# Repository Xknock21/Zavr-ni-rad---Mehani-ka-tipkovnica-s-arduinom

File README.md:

# Zavrsni rad Mehanicka tipkovnica s arduinom

<h3>Shema</h3>

Shema tipkovnicje korisit matriks koji gleda koja je tipka pritisnuta u bilo kojem vrenu te ta se informacija šalje arduinu te on računalu šalje podatak koja je tipka pritisnuta i što bi on trebao ispisati.

<h3>PCB</h3> 

Napravio sam PCB-u besplatnom programu KiCad 7.0, a izradu PCB-a je odradio JLCPCB.

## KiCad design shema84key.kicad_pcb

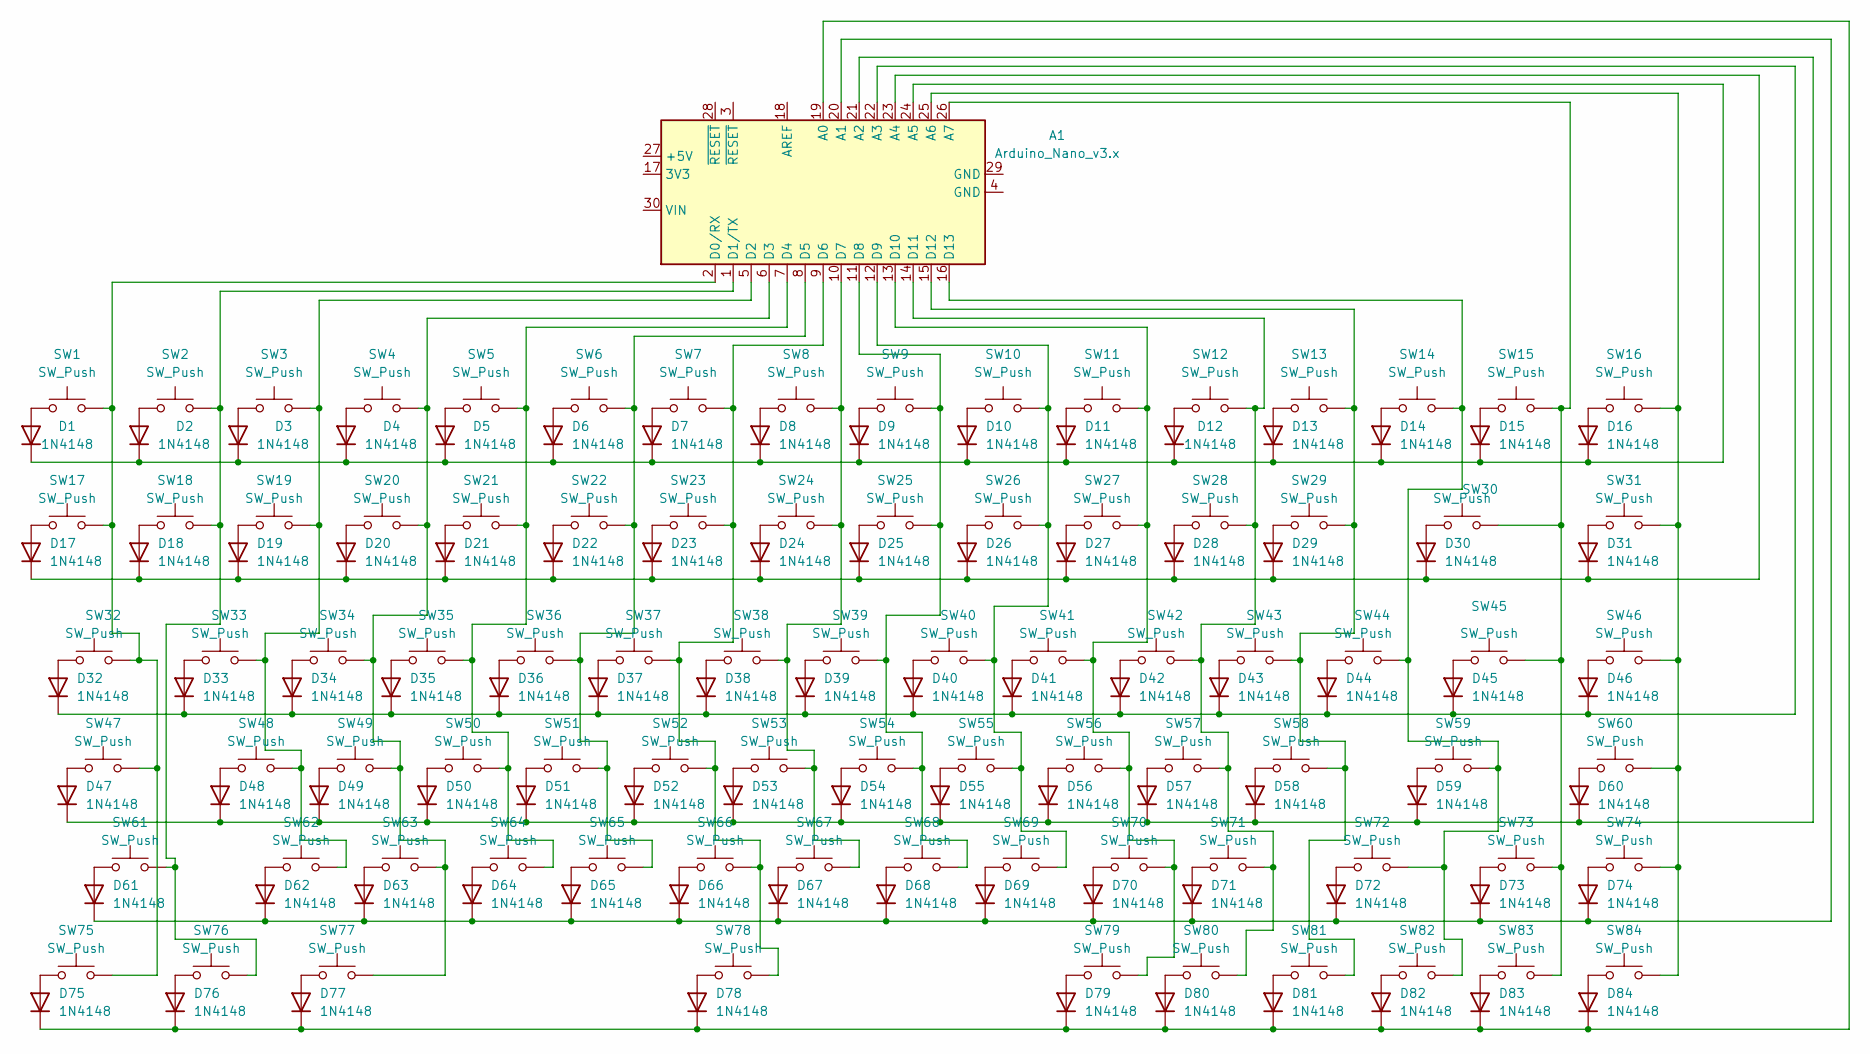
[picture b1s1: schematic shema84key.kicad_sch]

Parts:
A1: Arduino_Nano_v3.x; Arduino_Nano
D1, D2, D3, D4, D5, D6, D7, D8, D9, D10, D11, D12, D13, D14, D15, D16, D17, D18, D19, D20, D21, D22, D23, D24, D25, D26, D27, D28, D29, D30, D31, D32, D33, D34, D35, D36, D37, D38, D39, D40, D41, D42, D43, D44, D45, D46, D47, D48, D49, D50, D51, D52, D53, D54, D55, D56, D57, D58, D59, D60, D61, D62, D63, D64, D65, D66, D67, D68, D69, D70, D71, D72, D73, D74, D75, D76, D77, D78, D79, D80, D81, D82, D83, D84: 1N4148; D_DO-35_SOD27_P7.62mm_Horizontal
SW1, SW2, SW3, SW4, SW5, SW6, SW7, SW8, SW9, SW10, SW11, SW12, SW13, SW14, SW15, SW16, SW17, SW18, SW19, SW20, SW21, SW22, SW23, SW24, SW25, SW26, SW27, SW28, SW29, SW31, SW33, SW34, SW35, SW36, SW37, SW38, SW39, SW40, SW41, SW42, SW43, SW44, SW46, SW48, SW49, SW50, SW51, SW52, SW53, SW54, SW55, SW56, SW57, SW58, SW60, SW62, SW63, SW64, SW65, SW66, SW67, SW68, SW69, SW70, SW71, SW73, SW74, SW79, SW80, SW81, SW82, SW83, SW84: SW_Push; SW_Cherry_MX_1.00u_PCB
SW30: SW_Push; SW_Cherry_MX_2.00u_PCB
SW32, SW45: SW_Push; SW_Cherry_MX_1.50u_PCB
SW47, SW72: SW_Push; SW_Cherry_MX_1.75u_PCB
SW59, SW61: SW_Push; SW_Cherry_MX_2.25u_PCB
SW75, SW76, SW77: SW_Push; SW_Cherry_MX_1.25u_PCB
SW78: SW_Push; SW_Cherry_MX_6.25u_PCB

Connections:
unnamed: A1.19 (A0), D75.1 (K), D76.1 (K), D77.1 (K), D78.1 (K), D79.1 (K), D80.1 (K), D81.1 (K), D82.1 (K), D83.1 (K), D84.1 (K)
unnamed: A1.20 (A1), D61.1 (K), D62.1 (K), D63.1 (K), D64.1 (K), D65.1 (K), D66.1 (K), D67.1 (K), D68.1 (K), D69.1 (K), D70.1 (K), D71.1 (K), D72.1 (K), D73.1 (K), D74.1 (K)
unnamed: A1.21 (A2), D47.1 (K), D48.1 (K), D49.1 (K), D50.1 (K), D51.1 (K), D52.1 (K), D53.1 (K), D54.1 (K), D55.1 (K), D56.1 (K), D57.1 (K), D58.1 (K), D59.1 (K), D60.1 (K)
unnamed: A1.22 (A3), D32.1 (K), D33.1 (K), D34.1 (K), D35.1 (K), D36.1 (K), D37.1 (K), D38.1 (K), D39.1 (K), D40.1 (K), D41.1 (K), D42.1 (K), D43.1 (K), D44.1 (K), D45.1 (K), D46.1 (K)
unnamed: A1.23 (A4), D17.1 (K), D18.1 (K), D19.1 (K), D20.1 (K), D21.1 (K), D22.1 (K), D23.1 (K), D24.1 (K), D25.1 (K), D26.1 (K), D27.1 (K), D28.1 (K), D29.1 (K), D30.1 (K), D31.1 (K)
unnamed: A1.24 (A5), D1.1 (K), D2.1 (K), D3.1 (K), D4.1 (K), D5.1 (K), D6.1 (K), D7.1 (K), D8.1 (K), D9.1 (K), D10.1 (K), D11.1 (K), D12.1 (K), D13.1 (K), D14.1 (K), D15.1 (K), D16.1 (K)
unnamed: A1.25 (A6), SW16.2, SW31.2, SW46.2, SW60.2, SW74.2, SW84.2
unnamed: A1.2 (D0/RX), SW1.2, SW17.2, SW32.2, SW47.2, SW75.2
unnamed: A1.1 (D1/TX), SW2.2, SW18.2, SW61.2, SW76.2
unnamed: A1.5 (D2), SW3.2, SW19.2, SW33.2, SW48.2, SW62.2
unnamed: A1.6 (D3), SW4.2, SW20.2, SW34.2, SW49.2, SW63.2, SW77.2
unnamed: A1.7 (D4), SW5.2, SW21.2, SW35.2, SW50.2, SW64.2
unnamed: A1.8 (D5), SW6.2, SW22.2, SW36.2, SW51.2, SW65.2
unnamed: A1.9 (D6), SW7.2, SW23.2, SW37.2, SW52.2, SW66.2, SW78.2
unnamed: A1.10 (D7), SW8.2, SW24.2, SW38.2, SW53.2, SW67.2
unnamed: A1.11 (D8), SW9.2, SW25.2, SW39.2, SW54.2, SW68.2
unnamed: A1.12 (D9), SW10.2, SW26.2, SW40.2, SW55.2, SW69.2
unnamed: A1.13 (D10), SW11.2, SW27.2, SW41.2, SW56.2, SW70.2, SW79.2
unnamed: A1.14 (D11), SW12.2, SW28.2, SW42.2, SW57.2, SW71.2, SW80.2
unnamed: A1.15 (D12), SW13.2, SW29.2, SW43.2, SW58.2, SW81.2
unnamed: A1.16 (D13), SW14.2, SW44.2, SW59.2, SW72.2, SW82.2
unnamed: D1.2 (A), SW1.1
unnamed: D2.2 (A), SW2.1
unnamed: D3.2 (A), SW3.1
unnamed: D4.2 (A), SW4.1
unnamed: D5.2 (A), SW5.1
unnamed: D6.2 (A), SW6.1
unnamed: D7.2 (A), SW7.1
unnamed: D8.2 (A), SW8.1
unnamed: D9.2 (A), SW9.1
unnamed: D10.2 (A), SW10.1
unnamed: D11.2 (A), SW11.1
unnamed: D12.2 (A), SW12.1
unnamed: D13.2 (A), SW13.1
unnamed: D14.2 (A), SW14.1
unnamed: D15.2 (A), SW15.1
unnamed: D16.2 (A), SW16.1
unnamed: D17.2 (A), SW17.1
unnamed: D18.2 (A), SW18.1
unnamed: D19.2 (A), SW19.1
unnamed: D20.2 (A), SW20.1
unnamed: D21.2 (A), SW21.1
unnamed: D22.2 (A), SW22.1
unnamed: D23.2 (A), SW23.1
unnamed: D24.2 (A), SW24.1
unnamed: D25.2 (A), SW25.1
unnamed: D26.2 (A), SW26.1
unnamed: D27.2 (A), SW27.1
unnamed: D28.2 (A), SW28.1
unnamed: D29.2 (A), SW29.1
unnamed: D30.2 (A), SW30.1
unnamed: D31.2 (A), SW31.1
unnamed: D32.2 (A), SW32.1
unnamed: D33.2 (A), SW33.1
unnamed: D34.2 (A), SW34.1
unnamed: D35.2 (A), SW35.1
unnamed: D36.2 (A), SW36.1
unnamed: D37.2 (A), SW37.1
unnamed: D38.2 (A), SW38.1
unnamed: D39.2 (A), SW39.1
unnamed: D40.2 (A), SW40.1
unnamed: D41.2 (A), SW41.1
unnamed: D42.2 (A), SW42.1
unnamed: D43.2 (A), SW43.1
unnamed: D44.2 (A), SW44.1
unnamed: D45.2 (A), SW45.1
unnamed: D46.2 (A), SW46.1
unnamed: D47.2 (A), SW47.1
unnamed: D48.2 (A), SW48.1
unnamed: D49.2 (A), SW49.1
unnamed: D50.2 (A), SW50.1
unnamed: D51.2 (A), SW51.1
unnamed: D52.2 (A), SW52.1
unnamed: D53.2 (A), SW53.1
unnamed: D54.2 (A), SW54.1
unnamed: D55.2 (A), SW55.1
unnamed: D56.2 (A), SW56.1
unnamed: D57.2 (A), SW57.1
unnamed: D58.2 (A), SW58.1
unnamed: D59.2 (A), SW59.1
unnamed: D60.2 (A), SW60.1
unnamed: D61.2 (A), SW61.1
unnamed: D62.2 (A), SW62.1
unnamed: D63.2 (A), SW63.1
unnamed: D64.2 (A), SW64.1
unnamed: D65.2 (A), SW65.1
unnamed: D66.2 (A), SW66.1
unnamed: D67.2 (A), SW67.1
unnamed: D68.2 (A), SW68.1
unnamed: D69.2 (A), SW69.1
unnamed: D70.2 (A), SW70.1
unnamed: D71.2 (A), SW71.1
unnamed: D72.2 (A), SW72.1
unnamed: D73.2 (A), SW73.1
unnamed: D74.2 (A), SW74.1
unnamed: D75.2 (A), SW75.1
unnamed: D76.2 (A), SW76.1
unnamed: D77.2 (A), SW77.1
unnamed: D78.2 (A), SW78.1
unnamed: D79.2 (A), SW79.1
unnamed: D80.2 (A), SW80.1
unnamed: D81.2 (A), SW81.1
unnamed: D82.2 (A), SW82.1
unnamed: D83.2 (A), SW83.1
unnamed: D84.2 (A), SW84.1
Row 1: A1.26 (A7), SW15.2, SW30.2, SW45.2, SW73.2, SW83.2

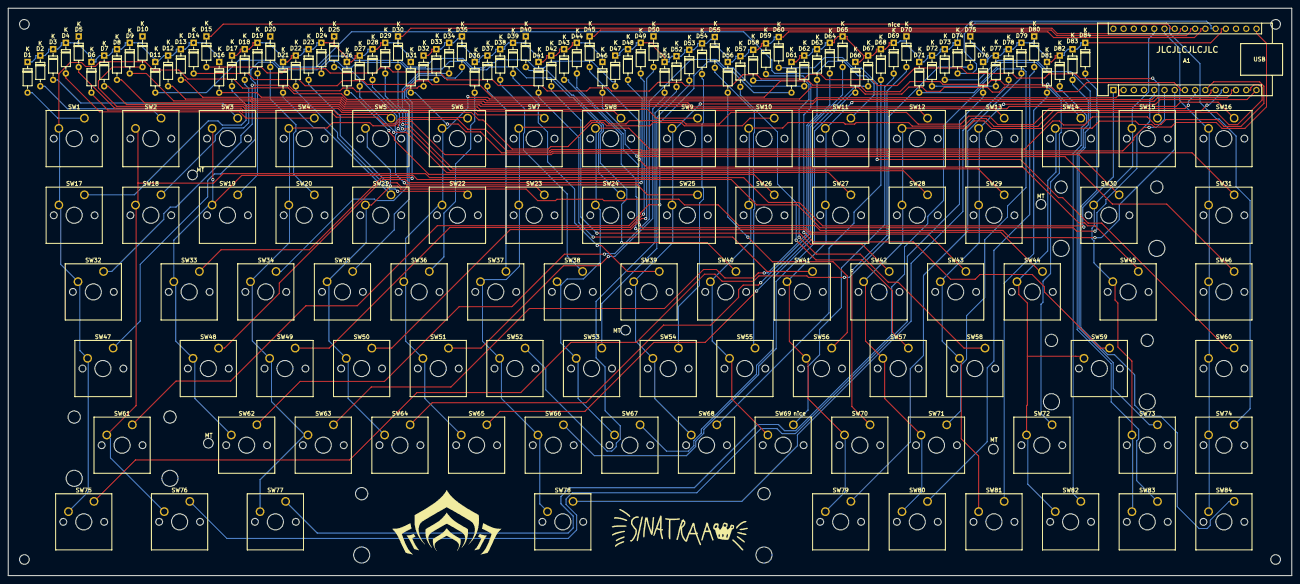
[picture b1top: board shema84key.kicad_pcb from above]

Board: 2 copper layers, 319.0 x 141.0 mm, 169 parts (0 on the bottom side), 106 nets.
